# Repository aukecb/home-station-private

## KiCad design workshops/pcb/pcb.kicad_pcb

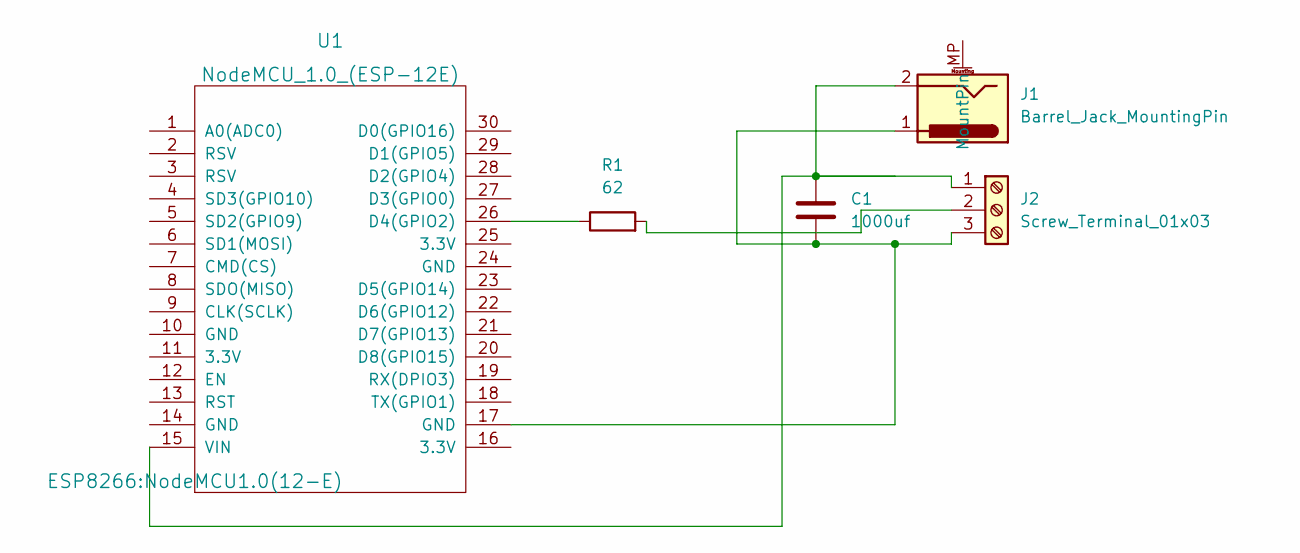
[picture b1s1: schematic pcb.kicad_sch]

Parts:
C1: 1000uf; CP_Radial_D10.0mm_P5.00mm
J1: Barrel_Jack_MountingPin; BarrelJack_Kycon_KLDX-0202-xC_Horizontal
J2: Screw_Terminal_01x03; TerminalBlock_bornier-3_P5.08mm
R1: 62; R_Axial_DIN0207_L6.3mm_D2.5mm_P10.16mm_Horizontal
U1: NodeMCU_1.0_(ESP-12E); NodeMCU1.0(12-E)

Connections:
unnamed: C1.1, J1.2, J2.1, U1.15 (VIN)
unnamed: C1.2, J1.1, J2.3, U1.17 (GND)
unnamed: R1.1, U1.26 (D4(GPIO2))
unnamed: J2.2, R1.2

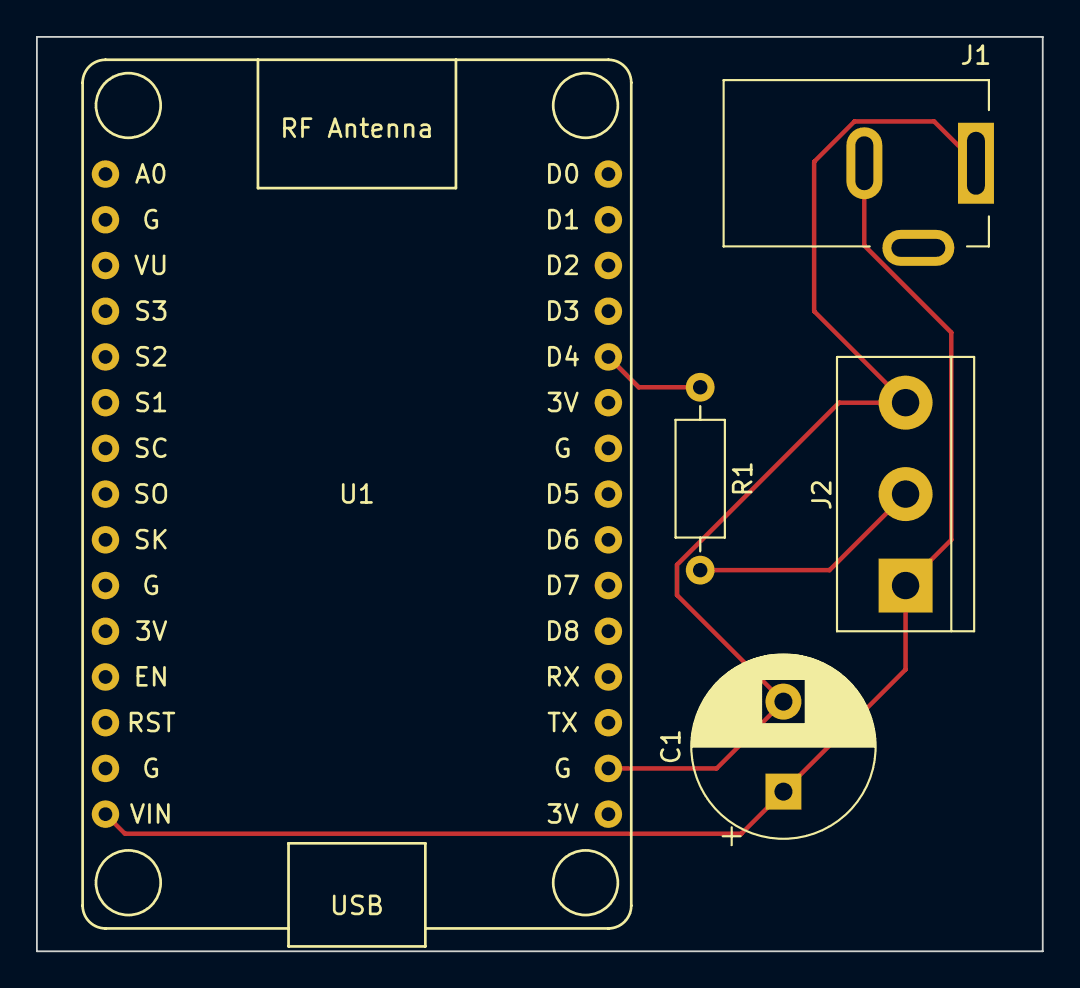
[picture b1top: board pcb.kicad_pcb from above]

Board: 2 copper layers, 55.9 x 50.8 mm, 5 parts (0 on the bottom side), 4 nets.

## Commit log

2023-10-10 initial submodule commit
2023-10-10 finished kph anenometer
2023-11-01 added screen code
2023-11-02 simpeler wind sensor
2023-11-12 last commit
